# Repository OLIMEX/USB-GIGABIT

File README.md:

# USB-GIGABIT
USB 1.1, USB 2.0, USB 3.0 to Ethernet 10/100/1000Mbit converter

Transfer troughput is up to 950Mbits/s when connected to USB 3.0 ports and GbE network.

Using the A20 OLinuXino boards and USB 2.0 host the speed is: upload 319 Mbit, download 295 Mbit.

## Commands
    iperf3 -c 192.168.0.xxx -p 2001 -t 3
    iperf3 -c 192.168.0.xxx -p 2001 -t 3 -R
    
## Empirical Test Results

Using the commands listed above and good grade Gigabit equipment.

| Board      |     Upload    |    Download   |
|------------|---------------|---------------|
| PC USB 3.0 | 933 Mbits/sec | 942 Mbits/sec |
| PC USB 2.0 | 290 Mbits/sec | 312 Mbits/sec |
| A20-MICRO  | 319 Mbits/sec | 295 Mbits/sec |

# License
- Hardware is released under CERN OHL v1.2 license
- Documentation is released under CC BY-SA 4.0 license

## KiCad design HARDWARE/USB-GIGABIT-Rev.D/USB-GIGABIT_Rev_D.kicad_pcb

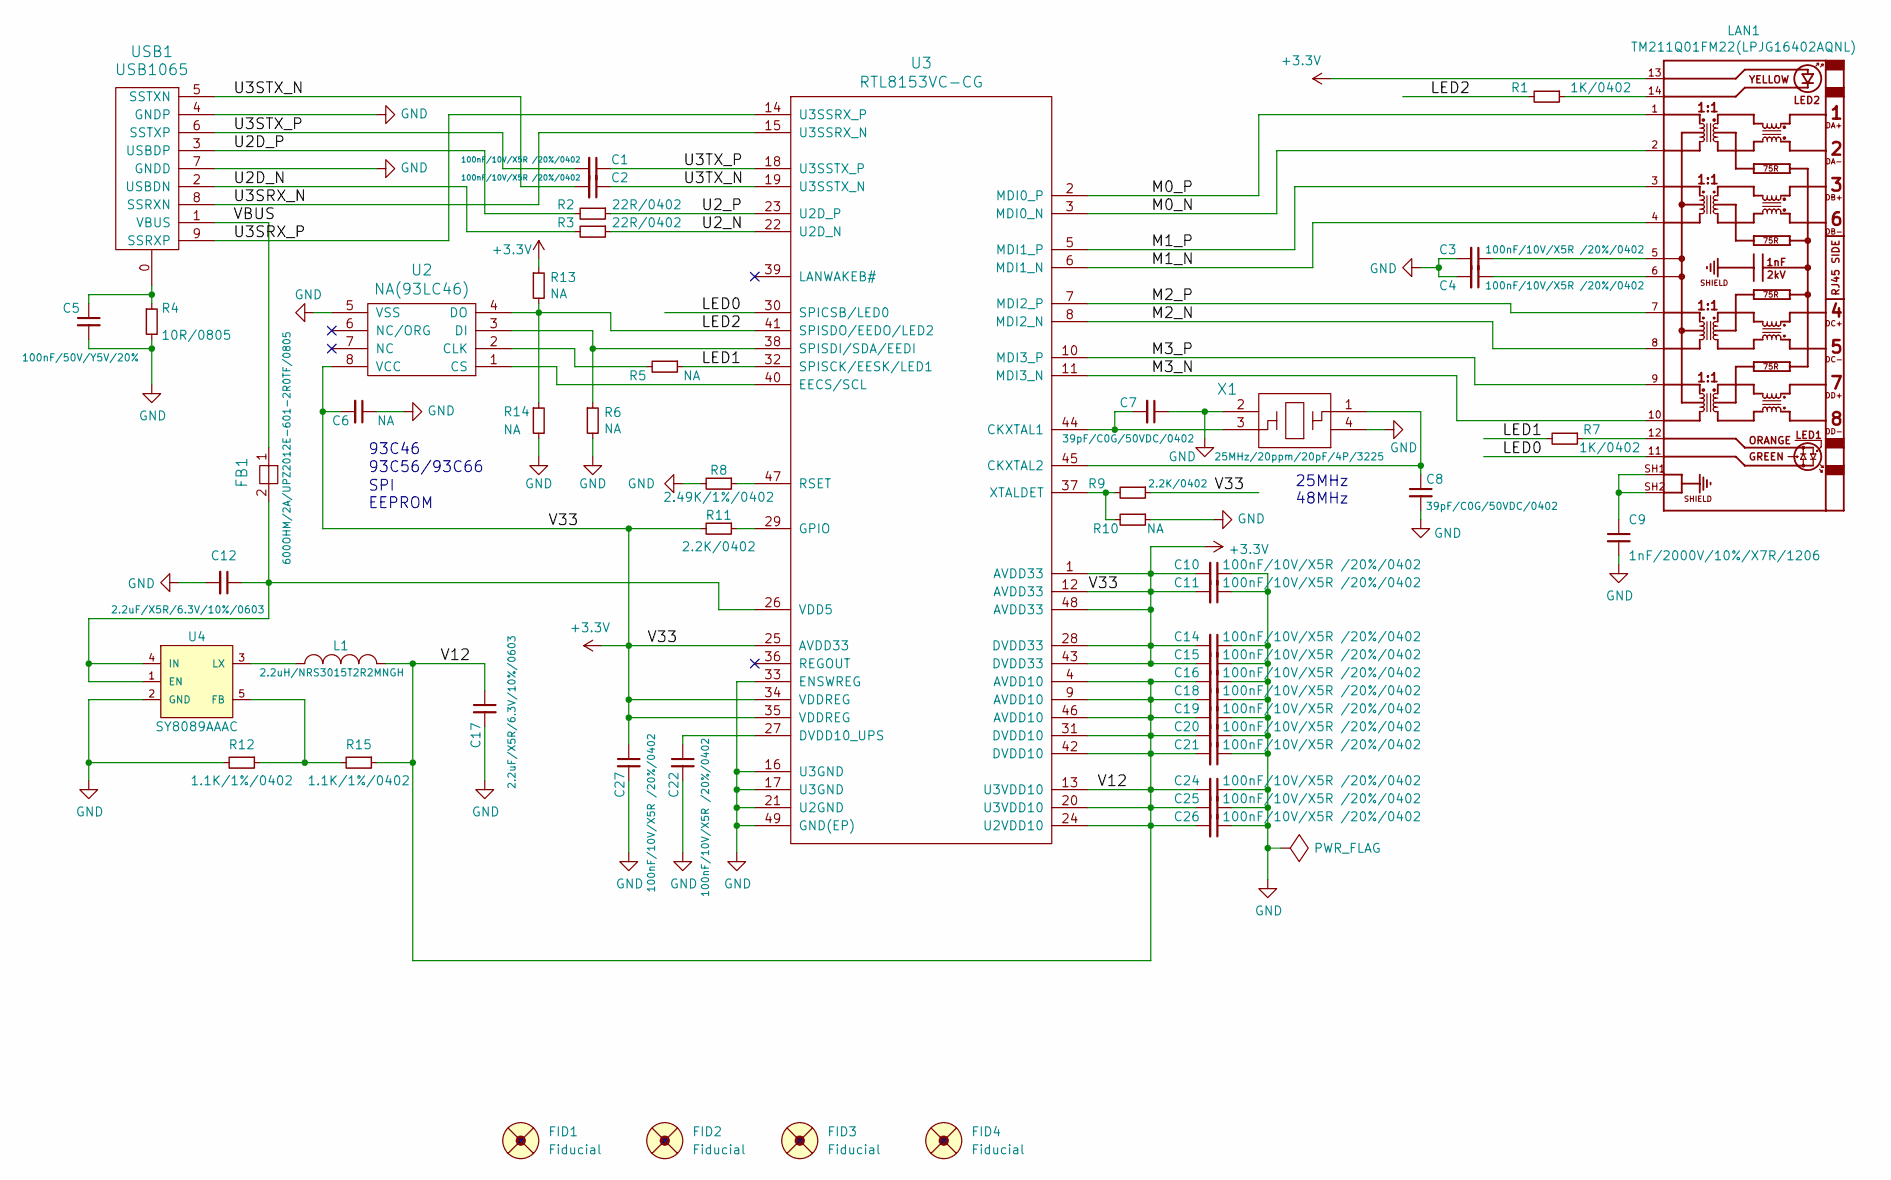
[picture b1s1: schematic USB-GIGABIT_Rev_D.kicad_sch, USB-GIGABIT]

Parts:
C1, C2, C3, C4, C10, C11, C14, C15, C16, C18, C19, C20, C21, C22, C24, C25, C26, C27: 100nF/10V/X5R /20%/0402; C_0402_5MIL_DWS
C5: 100nF/50V/Y5V/20%; C_0805_5MIL_DWS
C6: NA; C_0402_5MIL_DWS
C7, C8: 39pF/C0G/50VDC/0402; C_0402_5MIL_DWS
C9: 1nF/2000V/10%/X7R/1206; C_1206_5MIL_DWS_ISO
C12, C17: 2.2uF/X5R/6.3V/10%/0603; C_0603_5MIL_DWS
FB1: 600OHM/2A/UPZ2012E-601-2R0TF/0805; L_0805_5MIL_DWS
FID1, FID2: Fiducial; Fiducial1x3
FID3, FID4: Fiducial; Fiducial1x3_Paste
L1: 2.2uH/NRS3015T2R2MNGH; CD32
LAN1: TM211Q01FM22(LPJG16402AQNL); TM211Q01FM22
R1, R7: 1K/0402; R_0402_5MIL_DWS
R2, R3: 22R/0402; R_0402_5MIL_DWS
R4: 10R/0805; R_0805_5MIL_DWS
R5, R6, R10, R13, R14: NA; R_0402_5MIL_DWS
R8: 2.49K/1%/0402; R_0402_5MIL_DWS
R9, R11: 2.2K/0402; R_0402_5MIL_DWS
R12, R15: 1.1K/1%/0402; R_0402_5MIL_DWS
U2: NA(93LC46); SO-8
U3: RTL8153VC-CG; QFN48-6x6mm-OLIMEX_V2
U4: SY8089AAAC; SOT-23-5
USB1: USB1065; USB3_A_MALE
X1: 25MHz/20ppm/20pF/4P/3225; Oscillator-18.432MHz-3.2x2.5mm

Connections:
+3V3: C6.2, C10.2, C11.2, C14.2, C15.2, C27.1, LAN1.13, R9.1, R11.2, R13.1, U2.8 (VCC), U3.1 (AVDD33), U3.12 (AVDD33), U3.25 (AVDD33), U3.28 (DVDD33), U3.34 (VDDREG), U3.35 (VDDREG), U3.43 (DVDD33), U3.48 (AVDD33)
/LED0: LAN1.11, U3.30 (SPICSB/LED0)
/LED1: R5.1, R7.2, U3.32 (SPISCK/EESK/LED1)
/LED2: R1.2, R13.2, R14.1, U2.4 (DO), U3.41 (SPISDO/EEDO/LED2)
/M0_N: LAN1.2, U3.3 (MDI0_N)
/M0_P: LAN1.1, U3.2 (MDI0_P)
/M1_N: LAN1.4, U3.6 (MDI1_N)
/M1_P: LAN1.3, U3.5 (MDI1_P)
/M2_N: LAN1.8, U3.8 (MDI2_N)
/M2_P: LAN1.7, U3.7 (MDI2_P)
/M3_N: LAN1.10, U3.11 (MDI3_N)
/M3_P: LAN1.9, U3.10 (MDI3_P)
/U2D_N: R3.2, USB1.2 (USBDN)
/U2D_P: R2.2, USB1.3 (USBDP)
/U2_N: R3.1, U3.22 (U2D_N)
/U2_P: R2.1, U3.23 (U2D_P)
/U3SRX_N: U3.15 (U3SSRX_N), USB1.8 (SSRXN)
/U3SRX_P: U3.14 (U3SSRX_P), USB1.9 (SSRXP)
/U3STX_N: C2.2, USB1.5 (SSTXN)
/U3STX_P: C1.2, USB1.6 (SSTXP)
/U3TX_N: C2.1, U3.19 (U3SSTX_N)
/U3TX_P: C1.1, U3.18 (U3SSTX_P)
/V12: C16.2, C17.1, C18.2, C19.2, C20.2, C21.2, C24.2, C25.2, C26.2, L1.2, R15.1, U3.4 (AVDD10), U3.9 (AVDD10), U3.13 (U3VDD10), U3.20 (U3VDD10), U3.24 (U2VDD10), U3.31 (DVDD10), U3.42 (DVDD10), U3.46 (AVDD10)
/VBUS: FB1.1, USB1.1 (VBUS)
GND: C3.2, C4.2, C5.2, C6.1, C7.1, C8.2, C9.2, C10.1, C11.1, C12.2, C14.1, C15.1, C16.1, C17.2, C18.1, C19.1, C20.1, C21.1, C22.2, C24.1, C25.1, C26.1, C27.2, R4.2, R6.2, R8.2, R10.1, R12.2, R14.2, U2.5 (VSS), U3.16 (U3GND), U3.17 (U3GND), U3.21 (U2GND), U3.33 (ENSWREG), U3.49 (GND(EP)), U4.2 (GND), USB1.4 (GNDP), USB1.7 (GNDD), X1.2, X1.4
unnamed: C5.1, R4.1, USB1.0
unnamed: C9.1, LAN1.SH1, LAN1.SH2
unnamed: C3.1, LAN1.5
unnamed: C4.1, LAN1.6
unnamed: LAN1.12, R7.1
unnamed: LAN1.14, R1.1
unnamed: R5.2, U2.2 (CLK)
unnamed: U2.1 (CS), U3.40 (EECS/SCL)
unnamed: R6.1, U2.3 (DI), U3.38 (SPISDI/SDA/EEDI)
unnamed: C7.2, U3.44 (CKXTAL1), X1.3
unnamed: C8.1, U3.45 (CKXTAL2), X1.1
unnamed: C22.1, U3.27 (DVDD10_UPS)
unnamed: R11.1, U3.29 (GPIO)
unnamed: R8.1, U3.47 (RSET)
unnamed: C12.1, FB1.2, U3.26 (VDD5), U4.1 (EN), U4.4 (IN)
unnamed: R9.2, R10.2, U3.37 (XTALDET)
unnamed: R12.1, R15.2, U4.5 (FB)
unnamed: L1.1, U4.3 (LX)

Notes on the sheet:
93C56/93C66
25MHz 48MHz
SPI EEPROM
93C46

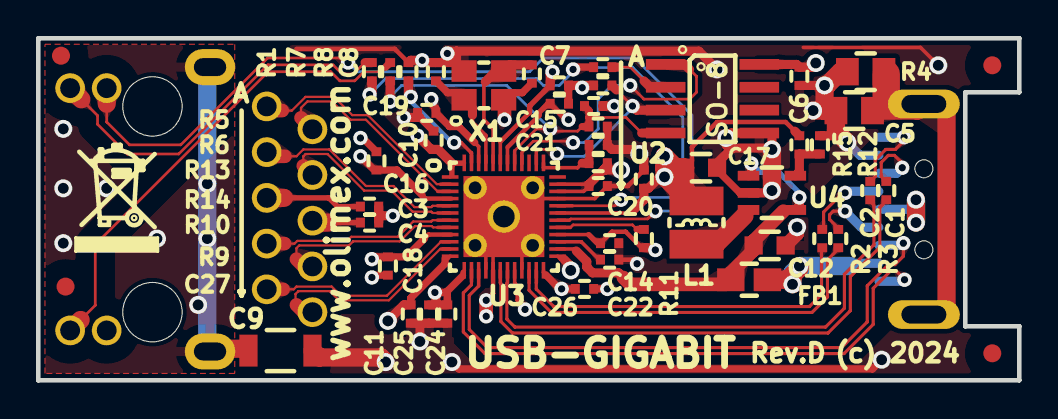
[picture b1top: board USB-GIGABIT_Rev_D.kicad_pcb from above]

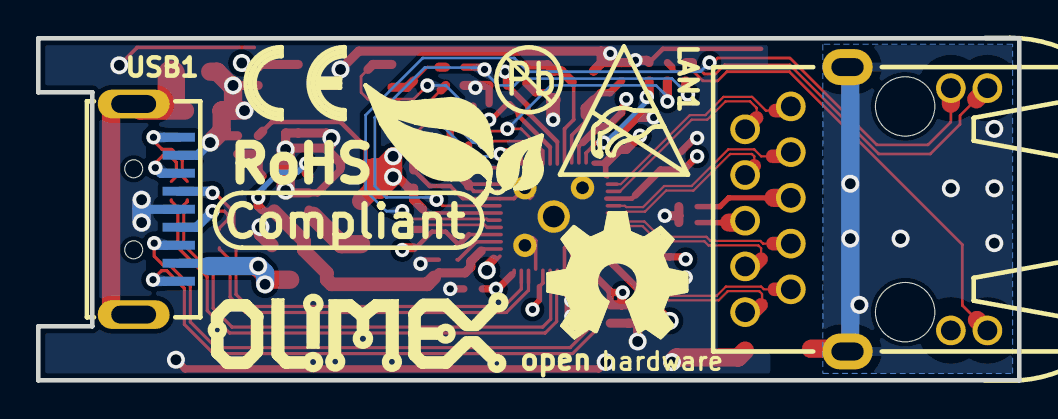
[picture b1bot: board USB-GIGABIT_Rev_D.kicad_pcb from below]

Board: 4 copper layers, 54.5 x 19.0 mm, 56 parts (6 on the bottom side), 43 nets.

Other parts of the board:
Logo_OLIMEX_TB: Logo_OLIMEX_TB
Sign_Antistatic: Sign_Antistatic
Sign_CE: CE_Sign
Sign_RoHS_1: Sign_RoHS_1

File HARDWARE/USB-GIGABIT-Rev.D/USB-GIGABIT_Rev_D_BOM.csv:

"Id";"Designator";"Footprint";"Quantity";"Designation";"Supplier and ref";
1;"C2,C3,C4,C10,C11,C14,C15,C16,C18,C19,C20,C21,C22,C24,C25,C26,C27,C1";"C_0402_5MIL_DWS";18;"100nF/10V/X5R /20%/0402";;;
2;"C5";"C_0805_5MIL_DWS";1;"100nF/50V/Y5V/20%";;;
3;"C6";"C_0402_5MIL_DWS";1;"NA";;;
4;"C7,C8";"C_0402_5MIL_DWS";2;"39pF/C0G/50VDC/0402";;;
5;"C9";"C_1206_5MIL_DWS_ISO";1;"1nF/2000V/10%/X7R/1206";;;
6;"C12,C17";"C_0603_5MIL_DWS";2;"2.2uF/X5R/6.3V/10%/0603";;;
7;"FB1";"L_0805_5MIL_DWS";1;" 600OHM/2A/UPZ2012E-601-2R0TF/0805";;;
8;"R2,R3";"R_0402_5MIL_DWS";2;"22R/0402";;;
9;"R4";"R_0805_5MIL_DWS";1;"10R/0805";;;
10;"R5,R6,R10,R13,R14";"R_0402_5MIL_DWS";5;"NA";;;
11;"R9,R11";"R_0402_5MIL_DWS";2;"2.2K/0402";;;
12;"U2";"SO-8";1;"NA(93LC46)";;;
13;"";"LOGO_RECYCLEBIN_1";1;"";;;
14;"U3";"QFN48-6x6mm-OLIMEX_V2";1;"RTL8153VC-CG";;;
15;"X1";"Oscillator-18.432MHz-3.2x2.5mm";1;"25MHz/20ppm/20pF/4P/3225";;;
16;"R1,R7";"R_0402_5MIL_DWS";2;"1K/0402";;;
17;"R8";"R_0402_5MIL_DWS";1;"2.49K/1%/0402";;;
18;"L1";"CD32";1;"2.2uH/NRS3015T2R2MNGH";;;
19;"R12,R15";"R_0402_5MIL_DWS";2;"1.1K/1%/0402";;;
20;"U4";"SOT-23-5";1;"SY8089AAAC";;;
21;"FID1,FID2";"Fiducial1x3";2;"Fiducial";;;
22;"FID4,FID3";"Fiducial1x3_Paste";2;"Fiducial";;;
23;"";"LOGO_OPENHARDWARE_8x8";1;"";;;
24;"";"LOGO_PBFREE";1;"";;;
25;"LAN1";"TM211Q01FM22";1;"TM211Q01FM22(LPJG16402AQNL)";;;
26;"USB1";"USB3_A_MALE";1;"USB1065";;;
27;"Sign_CE";"CE_Sign";1;"CE_Sign";;;
28;"Sign_Antistatic";"Sign_Antistatic";1;"Sign_Antistatic";;;
29;"Logo_OLIMEX_TB";"Logo_OLIMEX_TB";1;"Logo_OLIMEX_TB";;;
30;"Sign_RoHS_1";"Sign_RoHS_1";1;"Sign_RoHS_1";;;

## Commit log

2019-10-24 initial upload cad files
2024-12-16 Update
    Added latest hardware revisions.
2024-12-16 Update
    PDF exports and README.
2026-01-20 Update
    3D files

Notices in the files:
HARDWARE/USB-GIGABIT-Rev.D/USB-GIGABIT_Rev_D.kicad_pcb:
(c) 2024
